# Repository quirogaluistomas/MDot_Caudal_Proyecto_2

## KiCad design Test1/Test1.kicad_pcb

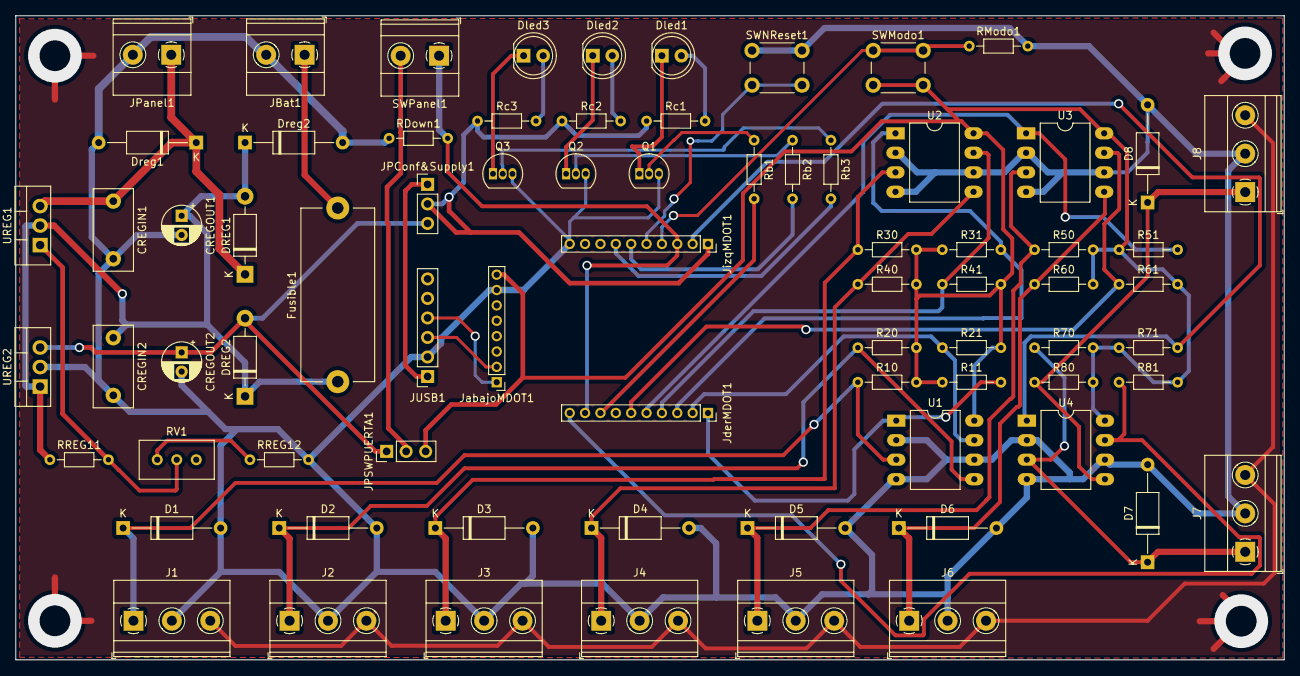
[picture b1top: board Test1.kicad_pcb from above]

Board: 2 copper layers, 165.1 x 83.8 mm, 75 parts (0 on the bottom side), 44 nets.

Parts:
CREGIN1: 100n; C_Disc_D10.5mm_W5.0mm_P7.50mm
CREGIN2: 0.47u; C_Disc_D10.5mm_W5.0mm_P7.50mm
CREGOUT1: 1u; CP_Radial_D5.0mm_P2.50mm
CREGOUT2: 22u; CP_Radial_D5.0mm_P2.50mm
D1, D2, D3, D4, D5, D6, D7, D8: D; D_A-405_P12.70mm_Horizontal
DREG1, DREG2: 1N4007; D_DO-41_SOD81_P10.16mm_Horizontal
Dled1, Dled2, Dled3: LED; LED_D5.0mm
Dreg1, Dreg2: D_Zener; D_A-405_P12.70mm_Horizontal
Fusible1: 1A, 25V; Fuseholder_Cylinder-5x20mm_Stelvio-Kontek_PTF78_Horizontal_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
J1, J2, J3, J4, J5, J6, J7, J8: Screw_Terminal_01x03; TerminalBlock_Phoenix_MKDS-1,5-3_1x03_P5.00mm_Horizontal
JBat1: Screw_Terminal_01x02; TerminalBlock_Phoenix_MKDS-1,5-2_1x02_P5.00mm_Horizontal
JPConf&Supply1: Jumper_3_Open; PinHeader_1x03_P2.54mm_Vertical
JPSWPUERTA1: Jumper_3_Open; PinHeader_1x03_P2.54mm_Vertical
JPanel1: Screw_Terminal_01x02; TerminalBlock_Phoenix_MKDS-1,5-2_1x02_P5.00mm_Horizontal
JUSB1: Conn_01x06_Female; PinSocket_1x06_P2.54mm_Vertical
JabajoMDOT1: Conn_01x08_Male; PinHeader_1x08_P2.00mm_Vertical
JderMDOT1: Conn_01x10_Female; PinSocket_1x10_P2.00mm_Vertical
JizqMDOT1: Conn_01x10_Female; PinSocket_1x10_P2.00mm_Vertical
Q1, Q2, Q3: BC337; TO-92_Inline
R10, R20, R30, R40, R50, R60, R70, R80: 1M; R_Axial_DIN0204_L3.6mm_D1.6mm_P7.62mm_Horizontal
R11, R21, R31, R41, R51, R61, R71, R81: 200k; R_Axial_DIN0204_L3.6mm_D1.6mm_P7.62mm_Horizontal
RDown1: 10k; R_Axial_DIN0204_L3.6mm_D1.6mm_P7.62mm_Horizontal
RModo1: 1k; R_Axial_DIN0204_L3.6mm_D1.6mm_P7.62mm_Horizontal
RREG11: 240; R_Axial_DIN0204_L3.6mm_D1.6mm_P7.62mm_Horizontal
RREG12: 1k; R_Axial_DIN0204_L3.6mm_D1.6mm_P7.62mm_Horizontal
RV1: 5k; Potentiometer_Bourns_3296W_Vertical
Rb1, Rb2, Rb3: 56k; R_Axial_DIN0204_L3.6mm_D1.6mm_P7.62mm_Horizontal
Rc1, Rc2, Rc3: 200; R_Axial_DIN0204_L3.6mm_D1.6mm_P7.62mm_Horizontal
SWModo1: SW_Push_Open_Dual; SW_PUSH_6mm_H4.3mm
SWNReset1: SW_Push_Open_Dual; SW_PUSH_6mm_H4.3mm
SWPanel1: SW_Push_Open_Dual; TerminalBlock_Phoenix_MKDS-1,5-2_1x02_P5.00mm_Horizontal
U1, U2, U3, U4: TS3V393_V1; DIP-8_W10.16mm_LongPads
UREG1: LM317_TO-252; TO-220-3_Vertical
UREG2: LM2931-5.0_TO220; TO-220-3_Vertical

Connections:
3VMdot: JPSWPUERTA1.3, JabajoMDOT1.8, R10.2, R11.1, R20.2, R21.2, R30.2, R31.1, R40.2, R41.2, R50.2, R51.1, R60.2, R61.2, R70.2, R71.1, R80.2, R81.2, SWModo1.2, U1.8, U2.8, U3.8, U4.8
5VUSB: JPConf&Supply1.1, JUSB1.1
+12V: CREGIN1.1, DREG1.1, Dreg1.1, JPanel1.1, UREG1.3
AI1: JderMDOT1.1, R11.2, U1.1
AI2: JderMDOT1.2, R21.1, U1.7
AI3: JderMDOT1.3, R31.2, U2.1
AI4: JderMDOT1.4, R41.1, U2.7
AI5: JderMDOT1.5, R51.2, U3.1
AI6: JderMDOT1.6, R61.1, U3.7
AI7: JizqMDOT1.2, R71.2, U4.1
AI8: JderMDOT1.10, R81.1, U4.7
DIPuerta: JderMDOT1.9, JizqMDOT1.3, RDown1.2, SWPanel1.1
DO1: JderMDOT1.8, Rb1.2
DO2: JizqMDOT1.6, Rb2.2
DO3: JizqMDOT1.7, Rb3.2
GND: CREGIN1.2, CREGIN2.2, CREGOUT1.2, CREGOUT2.2, D1.2, D2.2, D3.2, D4.2, D5.2, D6.2, D7.2, D8.2, Dreg1.2, Dreg2.2, J1.2, J2.2, J3.2, J4.2, J5.2, J6.2, J7.2, J8.2, JBat1.2, JPanel1.2, JUSB1.2, JabajoMDOT1.7, JizqMDOT1.10, Q1.3, Q2.3, Q3.3, RDown1.1, RModo1.2, RREG12.2, SWNReset1.1, U1.2, U1.4, U1.6, U2.2, U2.4, U2.6, U3.2, U3.4, U3.6, U4.2, U4.4, U4.6, UREG2.2
unnamed: D1.1, J1.1, R10.1, U1.3
unnamed: D2.1, J2.1, R20.1, U1.5
unnamed: D3.1, J3.1, R30.1, U2.3
unnamed: D4.1, J4.1, R40.1, U2.5
unnamed: D5.1, J5.1, R50.1, U3.3
unnamed: D6.1, J6.1, R60.1, U3.5
unnamed: D7.1, J7.1, R70.1, U4.3
unnamed: D8.1, J8.1, R80.1, U4.5
unnamed: Dled1.1, Q1.1
unnamed: Dled1.2, Rc1.2
unnamed: Dled2.1, Q2.1
unnamed: Dled2.2, Rc2.2
unnamed: Dled3.1, Q3.1
unnamed: Dled3.2, Rc3.2
unnamed: Fusible1.2, JBat1.1
unnamed: J1.3, J2.3, J3.3, J4.3, J5.3, J6.3, J7.3, J8.3
unnamed: JPSWPUERTA1.2, SWPanel1.2
unnamed: JUSB1.3, JabajoMDOT1.2
unnamed: JUSB1.4, JabajoMDOT1.1
unnamed: JizqMDOT1.4, RModo1.1, SWModo1.1
unnamed: JizqMDOT1.5, SWNReset1.2
unnamed: Q1.2, Rb1.1
unnamed: Q2.2, Rb2.1
unnamed: Q3.2, Rb3.1
unnamed: RREG11.2, RV1.1, RV1.2, UREG1.1
unnamed: RREG12.1, RV1.3
Vbat: CREGIN2.1, CREGOUT1.1, DREG1.2, DREG2.1, Dreg2.1, Fusible1.1, RREG11.1, UREG1.2, UREG2.1
VccMDOT: CREGOUT2.1, DREG2.2, JPConf&Supply1.2, JPConf&Supply1.3, JPSWPUERTA1.1, JizqMDOT1.1, Rc1.1, Rc2.1, Rc3.1, UREG2.3

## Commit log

2021-07-08 Armando el menu de configuración..
2021-07-25 Realizado hasta el envío de paquete. 25072021
2021-07-26 Realizado hasta envío de packets y cálculo de tiempos de sleep. 26072021
2021-07-28 Versión lista para prueba. Faltan ajustes igual
    Faltan ajustes del tipo de valores de limites random, variable sleemode en true, ver tema de eui, appkey, etc. En teoría debería al menos poder enviar datos al GW
2021-08-11 Actualización de pines y union con GW exitosa.
2021-08-15 Se agrega la parte de esquematico de PCB
2021-08-23 Este ya tiene el wake up por RTC o Interrupt
    Se le agrega el corte de panel
2021-08-25 Se agrega PCB Layout
    Falta rutear
2021-08-27 Cambios antes de comenzar a rutear
    Se modificaron algunas cosas en esquemático para comenzar a rutear.
2021-10-07 Avance hasta el dia de la fecha con placa soldada y enviando datos.
2021-10-07 Otro PCB con corrimiento de pines USB
2021-10-14 Hasta acá se arreglaron los problemas de K
    Funciona todo, envía ok, tanto caudal como frecuencia y se despierta si hay un cable cortado. Calcula correctamente y se puede configurar por usb. Falta probar panel conectado y luego la batería.
2021-10-26 Se agregan cosas muy útiles
    Se agrega última versión del programa junto con cosas de intro a proy que me van a servir. A su vez se hicieron las mediciones correspondientes con fotos.
2021-10-28 Se agrega el archivo de ProjectLibre
    Inicio del diagrama de Gant
2021-10-28 Resumen de las mediciones
2021-11-09 Planillas de costos
2021-11-24 Asignación de Recursos y Nuevos datos para economiua
2021-11-24 Nueva Asignación de recursos antes de reunión con tutor
2021-11-28 Principio de costos + Flows
2021-12-03 Avance en Costos y Grafana
2021-12-04 Agregado de gastos postventa de 10 kits
2021-12-04 Informe parcial
2021-12-07 Se cambiaron las torres metálicas por plásticas. Avance informe
2021-12-09 Avances
2021-12-11 Avance Proyecto
2021-12-17 Avance con cierre de Fact Economica
